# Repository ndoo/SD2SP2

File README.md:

# SD2SP2 Nano

This PCB allows a microSD card to be adapted into serial port 2 of the Nintendo GameCube.

### Bill of Materials

| Reference Designator | Part                                             | Digi-Key Part                                                                                                               |
|----------------------|--------------------------------------------------|-----------------------------------------------------------------------------------------------------------------------------|
| C1,C2                | Capacitor, Ceramic, 10µF, 16V, 0603              | [1276-6769-1-ND](https://www.digikey.com/product-detail/en/samsung-electro-mechanics/CL10X106MO8NRNC/1276-6769-1-ND/5961628) |
| J1                   | Connector, Micro SD Card, Push-Pull, Right Angle | [WM6825CT-ND](https://www.digikey.com/product-detail/en/molex/1050270001/WM6825CT-ND/3045221)                                |

### Ordering

The PCB must be ordered in 1.2mm thickness, with ENIG copper finish to ensure reliable electrical contact and minimal oxidation over time. I had my PCBs made at [JLCPCB](https://jlcpcb.com/).

The SD2SP2 Nano falls below the minimum board dimensions permitted by [Seeed Studio’s Fusion PCB service](http://www.seeedstudio.com/fusion_pcb.html), though panelizing the PCB can work around PCB fab houses which enforce a minimum size. I&rsquo;d actually recommend panelization, it would really drive down the cost of fabricating this tiny PCB.

### Assembly

Ideally, the PCB would be reflow-soldered, and all components were kept on a single side to make it a speedy affair. Hand-soldering instructions are provided below; the sample boards pictured above were hand soldered.

You will probably want (unless you are very skilled, patient and careful):

* Solder wick, to clean up solder bridges that may form across the narrowly-spaced pins of the microSD slot
* High-temperature (Kapton) tape to mask gold contacts from solder (accidentally tinning the gold contacts results in a non-reversible metallurgical reaction)

1. Solder C1 and C2 (they are non-polar and can be soldered in any orientation)
2. Place J1 on the PCB and solder pin 1 (pin farthest from gold plated connector)
3. Ensure J1&rsquo;s pins are precisely aligned; the small pitch will lead to pins shorting if misaligned (re-heat pin 1 as needed to reposition J1)
4. Use kapton tape to mask the longest gold plated connector on the top side, next to C1&rsquo;s silkscreen label
5. Solder the corner of J1&rsquo;s shield next to C1&rsquo;s silkscreen label
6. Solder the remaining pins of J1 - you may need solder wick to clean up solder bridges (P1-P5 and G1) across the closer-spaced pins
7. Solder the remaining shield corners of J1
8. Clean the board of any flux residue using isopropyl alcohol (or as directed by the flux/solder product you used)

### How it works

The EXI bus exposed from the GameCube&rsquo;s two serial ports uses an SPI-based protocol which is compatible with SD cards in SPI mode. [Swiss](https://github.com/emukidid/swiss-gc/releases) v0.4r682 or newer adds support for SD cards on serial port 2, identical to and in addition to existing memory card "SDGecko" adapter support.

The most common use-case for this seems to be using a &lt;4GB SD card in the SDGecko to load Swiss using Action Replay’s `autoexec.dol` feature, while using a larger microSD card in the SD2SP2 for storing homebrew and backups.

If you already have an IPL replacement modchip that boots into Swiss, or alternative loaders for Swiss such as the PSO exploit, then perhaps you may want an SD2SP2 for a cleaner front panel look for your GameCube, or to enable the use of 2 standard GameCube memory cards (which may be desirable for region switch consoles, as separate memory cards are needed between USA and JPN regions).

### Future Improvements

* Remove tented vias under silkscreen of "GC Front" text for aesthethic reasons
* Change the rounded edge of the connector to square edges, so that the board can be panelized adjacent to each other with V-cuts rather than requiring CNC milling
* Reduce the width of the microSD slot pads (P1-P5 and G1) and add a silkscreen barrier to prevent solder from bridging the pins during hand soldering

### Credits

This PCB was adapted from [citrus3000psi&rsquo;s original project](https://github.com/citrus3000psi/SD2SP2). I pruned previous revisions of the PCB from this repository, so please refer to the original repository for the original files.

The credits below are retained from the original README:

> Special thanks to:
> * MockyLock for the idea
> * Extrems & emu_kidid for doing the real work needed to make this possible

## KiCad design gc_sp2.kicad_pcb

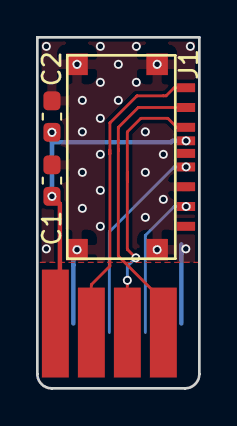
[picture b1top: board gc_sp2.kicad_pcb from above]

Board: 2 copper layers, 9.0 x 19.5 mm, 4 parts (0 on the bottom side), 7 nets.

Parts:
C1, C2: 10uF; C_0603_1608Metric_Pad1.05x0.95mm_HandSolder
J1: Micro_SD_Card; 1050270001
P1: SerialPort; SP2_FootPrint

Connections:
/3V3: C1.1, C2.1, J1.4, P1.1
/CLK: J1.5, P1.4
/CS: J1.2, P1.7
/DI: J1.3, P1.5
/DO: J1.7, P1.6
/INT: J1.1, P1.3
GND: C1.2, C2.2, J1.6, J1.9, P1.2, P1.8

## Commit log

2019-12-13 Add KiCad gitignore
2019-12-13 Add nano layout PCB
    PCB relayout for size reduction. PCB made rectangular for easier panelization and lower cost. 0806 22uF capacitor replaced with 2x 0603 10uF capacitor due to space limitations.
2020-01-02 Cleanup of non-Nano files, README updated and photos replaced
